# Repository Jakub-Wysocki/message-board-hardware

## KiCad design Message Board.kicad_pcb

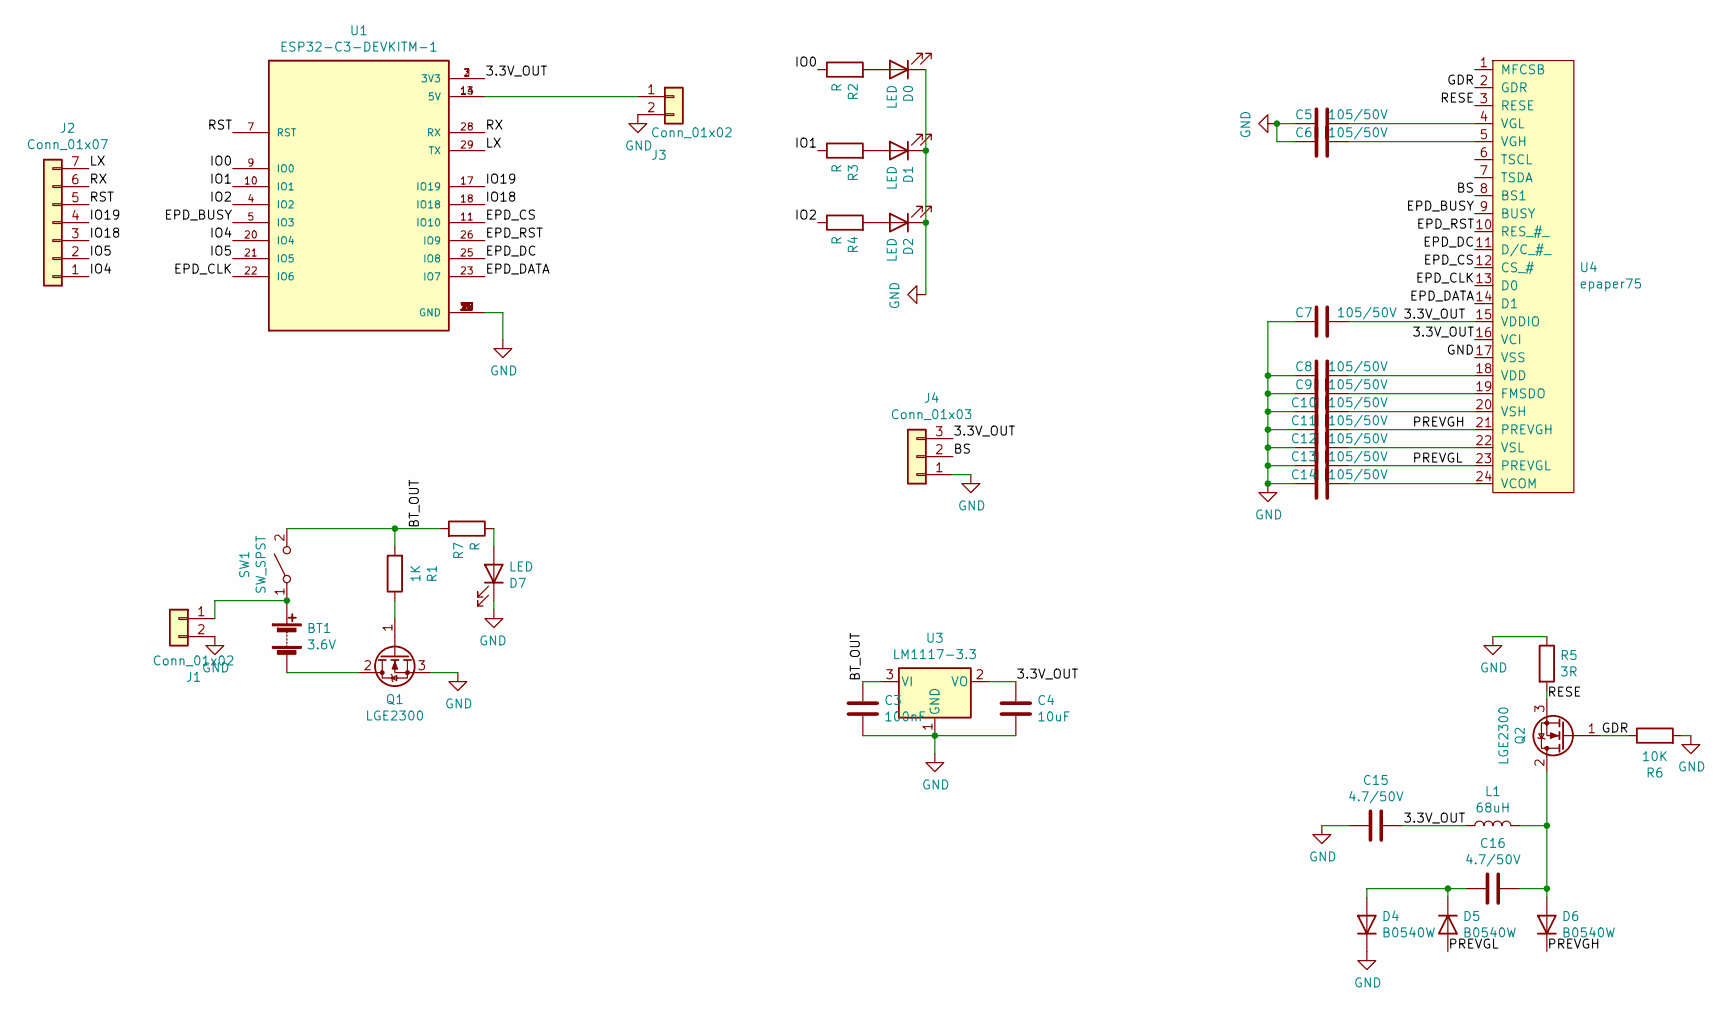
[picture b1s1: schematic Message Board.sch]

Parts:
BT1: 3.6V; BatteryHolder_Keystone_1042_1x18650
C3: 100nF; C_1206_3216Metric_Pad1.33x1.80mm_HandSolder
C4: 10uF; C_1206_3216Metric_Pad1.33x1.80mm_HandSolder
C5, C6, C7, C8, C9, C10, C11, C12, C13, C14: 105/50V; C_1206_3216Metric_Pad1.33x1.80mm_HandSolder
C15, C16: 4.7/50V; C_1206_3216Metric_Pad1.33x1.80mm_HandSolder
D0, D1, D2, D7: LED; LED_1206_3216Metric_Pad1.42x1.75mm_HandSolder
D4, D5, D6: B0540W; D_SOD-123
J1, J3: Conn_01x02; JST_EH_S2B-EH_1x02_P2.50mm_Horizontal
J2: Conn_01x07; JST_EH_S7B-EH_1x07_P2.50mm_Horizontal
J4: Conn_01x03; JST_EH_B3B-EH-A_1x03_P2.50mm_Vertical
L1: 68uH; L_12x12mm_H6mm
Q1, Q2: LGE2300; TSOT-23
R1: 1K; R_1206_3216Metric_Pad1.30x1.75mm_HandSolder
R2, R3, R4, R7: R; R_1206_3216Metric_Pad1.30x1.75mm_HandSolder
R5: 3R; R_1206_3216Metric_Pad1.30x1.75mm_HandSolder
R6: 10K; R_1206_3216Metric_Pad1.30x1.75mm_HandSolder
SW1: SW_SPST
U1: ESP32-C3-DEVKITM-1; XCVR_ESP32-C3-DEVKITM-1
U3: LM1117-3.3; SOT-223
U4: epaper75

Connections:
/3.3V_OUT: C4.1, C7.1, C15.1, J4.3, L1.1, U1.2 (3V3), U1.3 (3V3), U3.2 (VO), U4.15 (VDDIO), U4.16 (VCI)
/BS: J4.2, U4.8 (BS1)
/BT_OUT: C3.1, R1.2, R7.2, SW1.2 (B), U3.3 (VI)
/EPD_BUSY: U1.5 (IO3), U4.9 (BUSY)
/EPD_CLK: U1.22 (IO6), U4.13 (D0)
/EPD_CS: U1.11 (IO10), U4.12 (CS_#)
/EPD_DATA: U1.23 (IO7), U4.14 (D1)
/EPD_DC: U1.25 (IO8), U4.11 (D/C_#_)
/EPD_RST: U1.26 (IO9), U4.10 (RES_#_)
/GDR: Q2.1 (G), R6.1, U4.2 (GDR)
/IO0: R2.1, U1.9 (IO0)
/IO1: R3.1, U1.10 (IO1)
/IO2: R4.1, U1.4 (IO2)
/IO4: J2.1, U1.20 (IO4)
/IO5: J2.2, U1.21 (IO5)
/IO18: J2.3, U1.18 (IO18)
/IO19: J2.4, U1.17 (IO19)
/LX: J2.7, U1.29 (TX)
/PREVGH: C11.1, D6.1 (K), U4.21 (PREVGH)
/PREVGL: C13.1, D5.2 (A), U4.23 (PREVGL)
/RESE: Q2.3 (S), R5.2, U4.3 (RESE)
/RST: J2.5, U1.7 (RST)
/RX: J2.6, U1.28 (RX)
GND: C3.2, C4.2, C5.2, C6.2, C7.2, C8.2, C9.2, C10.2, C11.2, C12.2, C13.2, C14.2, C15.2, D0.1 (K), D1.1 (K), D2.1 (K), D4.1 (K), D7.1 (K), J1.2, J3.2, J4.1, Q1.3 (S), R5.1, R6.2, U1.1 (GND), U1.6 (GND), U1.8 (GND), U1.12 (GND), U1.15 (GND), U1.16 (GND), U1.19 (GND), U1.24 (GND), U1.27 (GND), U1.30 (GND), U3.1 (GND), U4.17 (VSS)
unnamed: BT1.1 (+), J1.1, SW1.1 (A)
unnamed: BT1.2 (-), Q1.2 (D)
unnamed: C5.1, U4.4 (VGL)
unnamed: C6.1, U4.5 (VGH)
unnamed: C8.1, U4.18 (VDD)
unnamed: C9.1, U4.19 (FMSDO)
unnamed: C10.1, U4.20 (VSH)
unnamed: C12.1, U4.22 (VSL)
unnamed: C14.1, U4.24 (VCOM)
unnamed: C16.1, D6.2 (A), L1.2, Q2.2 (D)
unnamed: C16.2, D4.2 (A), D5.1 (K)
unnamed: D0.2 (A), R2.2
unnamed: D1.2 (A), R3.2
unnamed: D2.2 (A), R4.2
unnamed: D7.2 (A), R7.1
unnamed: J3.1, U1.13 (5V), U1.14 (5V)
unnamed: Q1.1 (G), R1.1

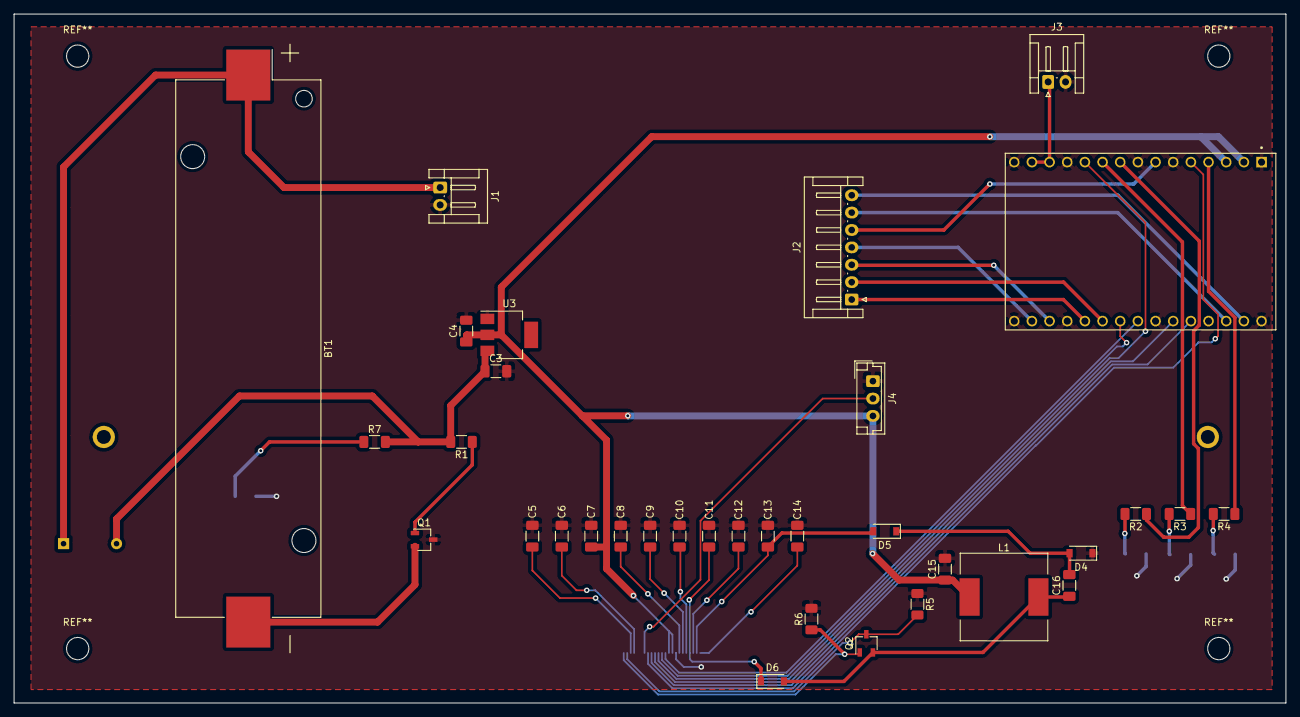
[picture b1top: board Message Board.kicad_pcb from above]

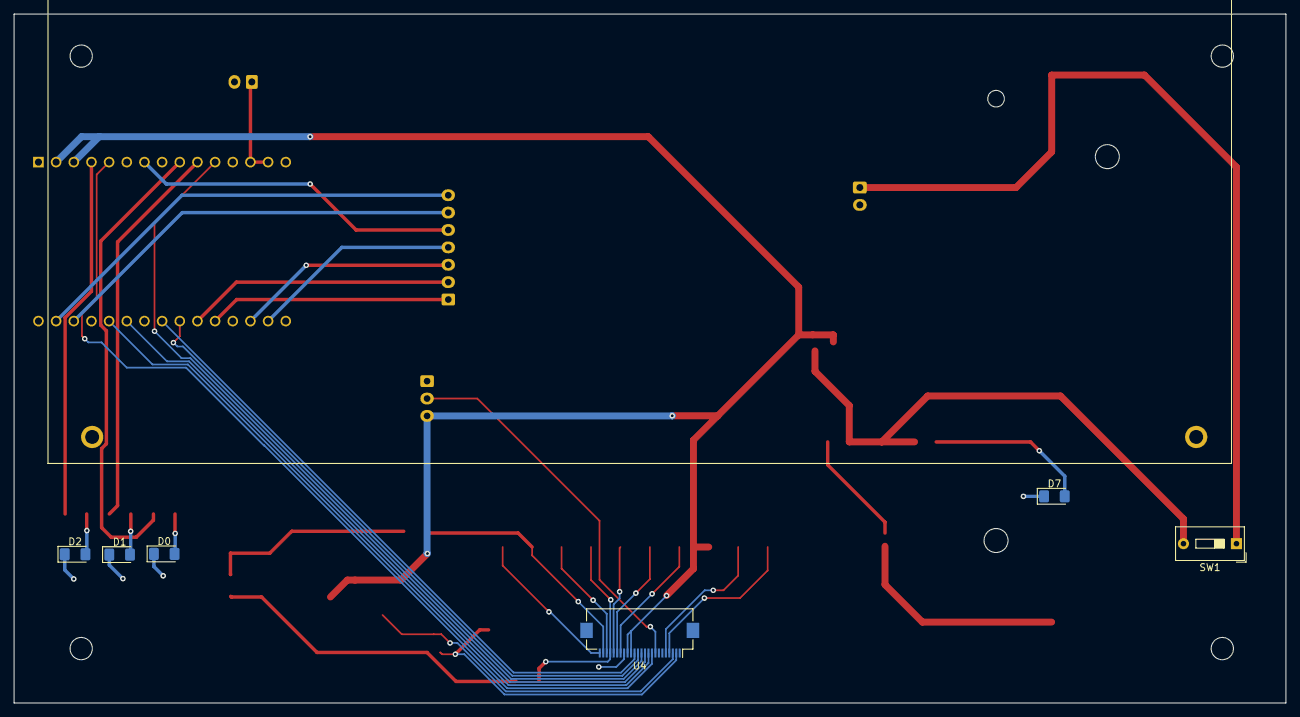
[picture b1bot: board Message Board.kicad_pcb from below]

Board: 2 copper layers, 182.9 x 99.1 mm, 40 parts (6 on the bottom side), 41 nets.

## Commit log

2022-02-14 Changed orientation of the FFC connector, battery from 2x18650 to 1x18650, devboard to ESP32-C3-DEVKITM-1 and updated the epaper footprint. Deleted second linear regualtor
2022-02-20 Updated SPI connections, added hardware possibility to chose if 3 or 4 SPI version (BS Pin)
